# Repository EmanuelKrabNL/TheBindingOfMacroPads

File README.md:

# TheBindingOfMacropads

A 6-key macropad with a rotary encoder and a 0.91" OLED display, built around a Seeed XIAO RP2040. Made as part of the [Hack Club Hackpad](https://hackpad.hackclub.com), for the Stardance YSWS program.

## Features:
- 6 macro keys, arrow-key style layout
- EC11-style rotary encoder — volume control, click to mute, etc.
- 0.91" 128x32 OLED display (I2C)
- QMK firmware
- VIAL Support
- OLED support
- Different presets (Discord, The binding of isaac, spotify, OBS, snake, timer and flappy bird.
- Konami code (up up down down left right left right), long press rotary encoder to see credits.
- Small tboi themed icons, isaac will sleep after a minute of inactivity.

## Why did i make this?
I have a 60% keyboard, so i cant use WASD and arrows together, so i made this board so i could play the binding of isaac! 

## CAD Model:

## PCB
Made in kicad.

Schematic

PCB

## Firmware Overview
This hackpad uses [QMK](https://qmk.fm/) firmware.

- The rotary encoder controls volume. Click to mute.
- The 6 keys are mapped to arrow keys, space and E by default.

## BOM:
- 1x Seeed XIAO RP2040
- 1x 0.91" 128x32 OLED display (I2C, SSD1306-compatible)
- 6x Cherry MX Switches
- 6x DSA Keycaps
- 1x EC11 rotary encoder
- 1x Case (2 printed parts)

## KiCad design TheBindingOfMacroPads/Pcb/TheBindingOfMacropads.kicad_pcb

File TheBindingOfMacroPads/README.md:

STILL WORKING ON EVERYTHING!!
really short description:
For the people who want to play The Binding Of Isaac on a 60 percent keyboard, and dont like the rebinds...

another small test to see if everything is working, dont mind this!

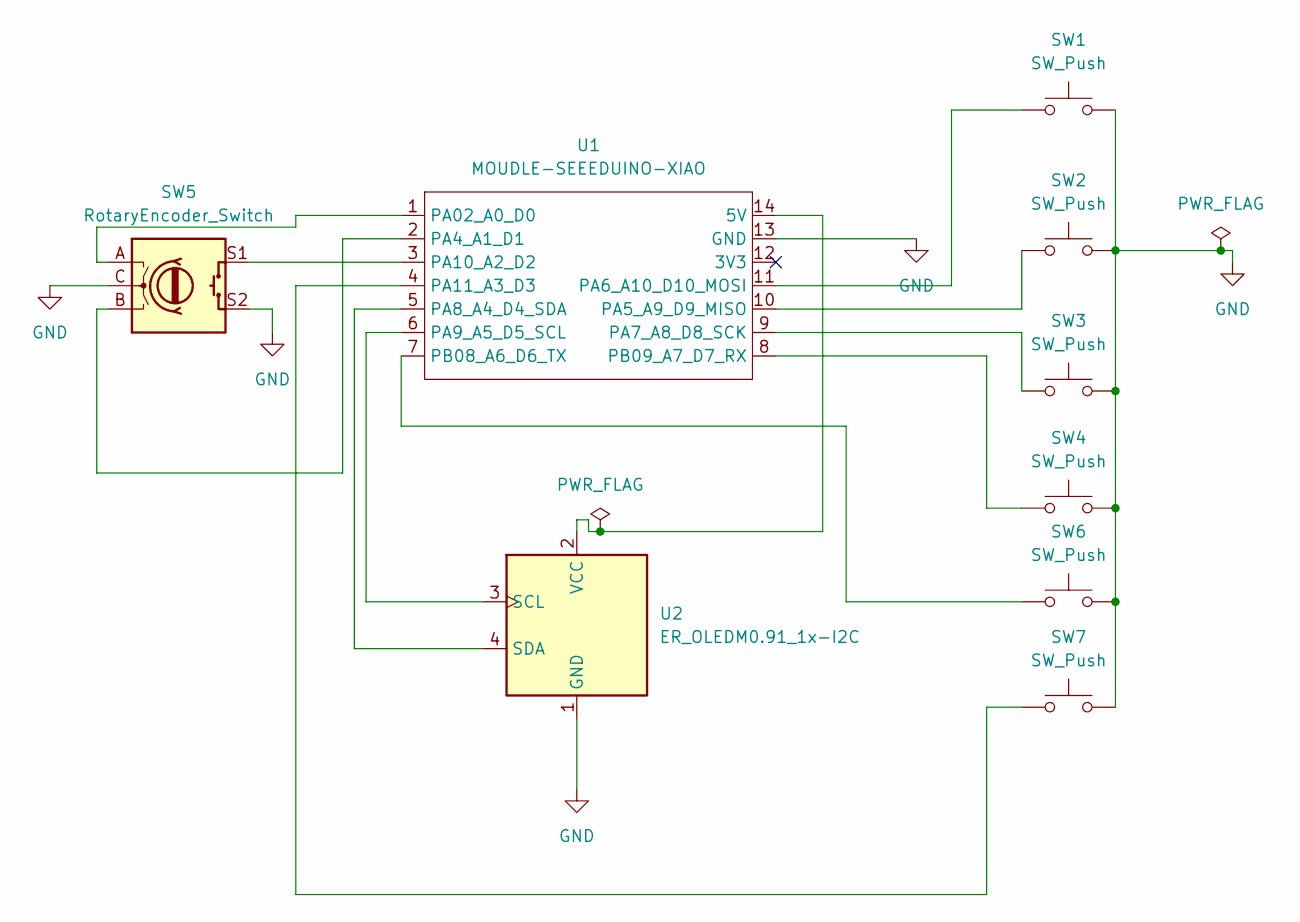
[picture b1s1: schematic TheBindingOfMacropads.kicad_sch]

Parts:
SW1, SW2, SW3, SW4, SW6, SW7: SW_Push; SW_Cherry_MX_1.00u_PCB
SW5: RotaryEncoder_Switch; RotaryEncoder_Alps_EC11E-Switch_Vertical_H20mm
U1: MOUDLE-SEEEDUINO-XIAO; XIAO-Generic-Hybrid-14P-2.54-21X17.8MM
U2: ER_OLEDM0.91_1x-I2C

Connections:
GND: SW1.2, SW2.2, SW3.2, SW4.2, SW5.C, SW5.S2, SW6.2, SW7.2, U1.13 (GND), U2.1 (GND)
unnamed: U1.14 (5V), U2.2 (VCC)
unnamed: SW5.A, U1.1 (PA02_A0_D0)
unnamed: SW5.B, U1.2 (PA4_A1_D1)
unnamed: SW2.1, U1.10 (PA5_A9_D9_MISO)
unnamed: SW1.1, U1.11 (PA6_A10_D10_MOSI)
unnamed: SW3.1, U1.9 (PA7_A8_D8_SCK)
unnamed: U1.5 (PA8_A4_D4_SDA), U2.4 (SDA)
unnamed: U1.6 (PA9_A5_D5_SCL), U2.3 (SCL)
unnamed: SW5.S1, U1.3 (PA10_A2_D2)
unnamed: SW7.1, U1.4 (PA11_A3_D3)
unnamed: SW6.1, U1.7 (PB08_A6_D6_TX)
unnamed: SW4.1, U1.8 (PB09_A7_D7_RX)

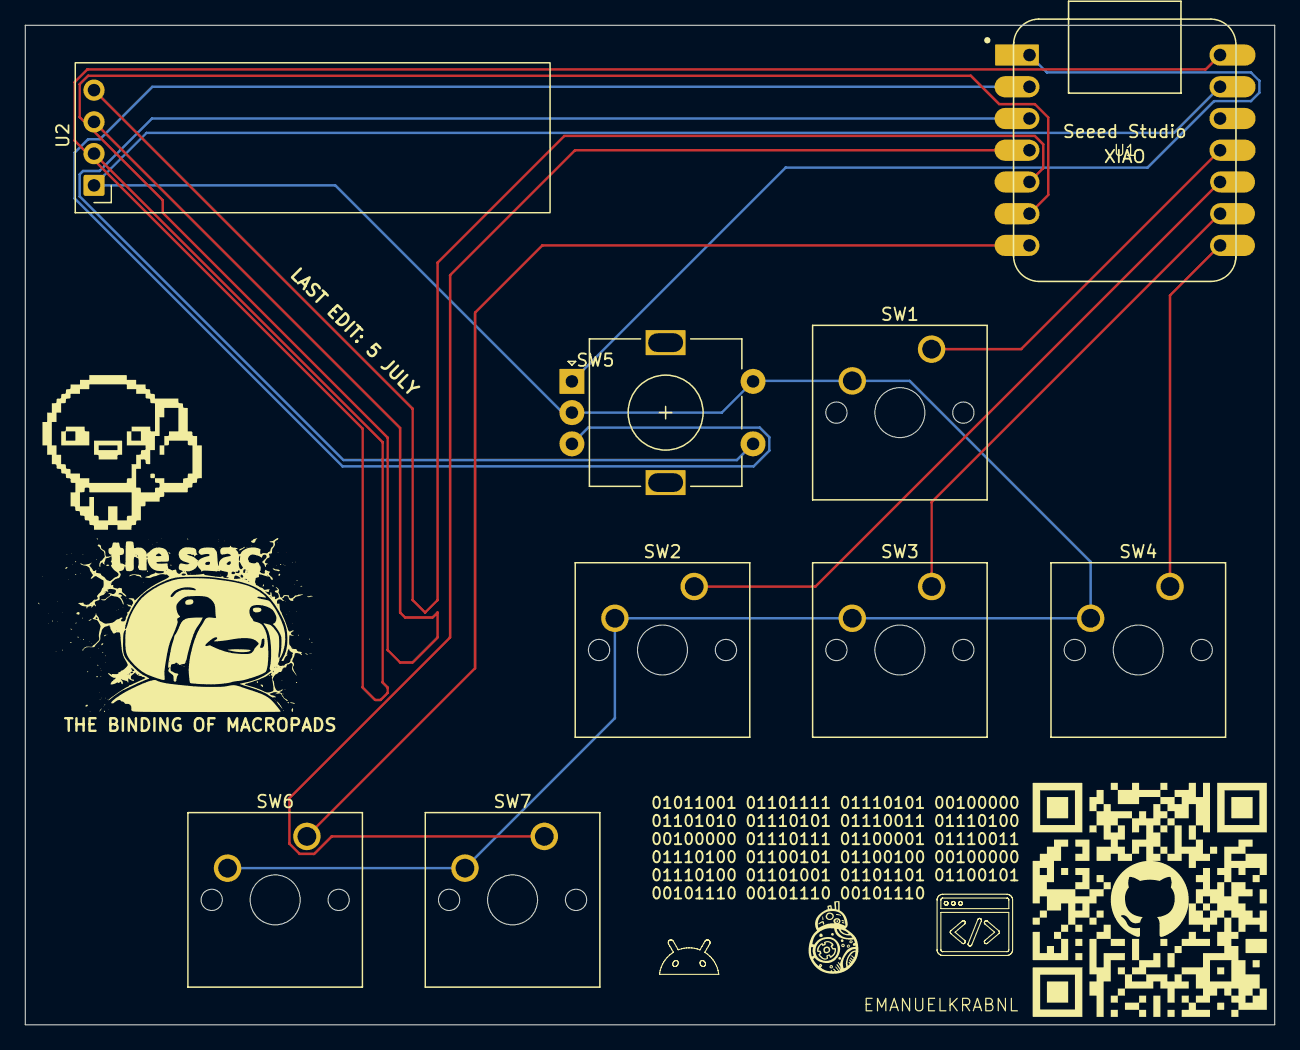
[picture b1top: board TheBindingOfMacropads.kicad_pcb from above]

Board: 2 copper layers, 100.0 x 80.0 mm, 9 parts (0 on the bottom side), 13 nets.

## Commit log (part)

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2026-06-26 Add initial README with project description
2026-06-26 small test
